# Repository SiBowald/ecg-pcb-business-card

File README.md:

# ECG PCB Business Card

## Table of contents

- [ECG PCB Business Card](#ecg-pcb-business-card)
  - [Intended use / disclaimer](#intended-use--disclaimer)
  - [Battery safety](#battery-safety)
  - [What the card does](#what-the-card-does)
  - [Compatibility (important)](#compatibility-important)
  - [Quick start (battery recommended)](#quick-start-battery-recommended)
  - [How to hold it (signal quality)](#how-to-hold-it-signal-quality)
  - [Powering via NFC energy harvesting (Android only)](#powering-via-nfc-energy-harvesting-android-only)
  - [What you should see](#what-you-should-see)
  - [Files & documentation](#files--documentation)
    - [Project structure](#project-structure)
    - [Running the web app locally](#running-the-web-app-locally)
  - [Quick troubleshooting](#quick-troubleshooting)
  - [Key ICs used](#key-ics-used)
  - [License](#license)
  - [Sponsorship](#sponsorship)

Educational demo: a functional single-lead ECG front end on a business-card-sized PCB.  
It streams the signal to your phone or computer using frequency-modulated ultrasound, decoded in a browser-based web app.

Goal: power it up, open the web app, and see a clean ECG-like waveform within about a minute, without any special lab setup.

---

## Intended use / disclaimer

**This is a DIY educational demo and not a medical device.**  
It is not intended for diagnosis, monitoring, or clinical decisions.

---

## Battery safety

The CR1220 coin cell may be outside of its original packaging. Coin cell batteries are hazardous if swallowed, so **keep them away from children at all times**.

---

## What the card does

- Measures a single-lead ECG using the built-in left/right finger pads
- Streams the signal to a web application via **ultrasound** (microphone permission required)
- Power options:
  - **Battery (recommended)**
  - **NFC energy harvesting (Android only)**

---

## Compatibility (important)

- **iOS:** works best with **Safari**
- **Android:** works best with **Chrome**
- **NFC energy harvesting:** works **only on Android**
  - iOS does not provide a reliable continuous NFC power mode for this use
- If powering via NFC energy harvesting, the phone **must not be charging** (unplug it)

---

## Quick start (battery recommended)

1. **Insert a 3 V CR1220 battery** (rated for at least **500 µA continuous load**).  
   Ensure the **+ (positive) side** faces the same direction as the **+** symbols on the PCB.  
   Do not bend the arms of the PCB battery holder more than necessary.  
   Idle current is **below 1 µA**, so the battery can be left in the holder.

2. **Open the web app**
   - Easiest: tap the phone to the card to open the link (NFC enabled + phone unlocked)
   - Scan the printed QR code
   - Or run locally (see **Files & documentation** below)

3. **In the web application**
   - Press **Start**
   - Allow **microphone access** when prompted

---

## How to hold it (signal quality)

- Place the phone/laptop on a table and rest your elbows to reduce motion.
- Hold the card firmly and press your thumbs onto the pads:
  - Left thumb on the pad marked with the hand icon and **“L”**
  - Right thumb on the pad marked with the hand icon and **“R”**
- Stay still and relax your hands and shoulders (movement causes artifacts).
- Keep the phone close to the card so the microphone picks up the signal reliably.
- Use a quiet room if possible (avoid talking, music, fans, strong background noise).
- Avoid Bluetooth headsets so the browser uses the built-in microphone.

---

## Powering via NFC energy harvesting (Android only)

Use this when you want a “no battery” demo. It is more sensitive to positioning.

1. Make sure the phone is **not charging** (unplug it).
2. Place the card on the **back of the phone**, centered over the phone’s **NFC coil** area.
3. Flip the card upside down as needed so Left/Right orientation is correct while it sits on the phone.
4. Press fingers on the same **L** and **R** pads as in battery mode.
5. If your phone has a metal frame/back, avoid touching metal parts while contacting the pads.

---

## What you should see

You should see a waveform similar to the example printed on the back of the card (below “This is not a medical device.”).

If the signal looks noisy or flat, it is almost always due to:
- Contact pressure
- Hand motion
- Dry skin
- NFC positioning (in harvesting mode)

---

## Files & documentation

### Project structure

- `hardware/ECG_Business_Card/`  
  KiCad project including the schematic, PCB layout, manufacturing files, and documentation assets.

- `web/`  
  Browser-based ECG decoder and viewer.

### Web app

The ECG monitor can be used either locally or directly through GitHub Pages.

**Online:**  
[Open the Ultrasound-based ECG Monitor](https://sibowald.github.io/ecg-pcb-business-card/)

**Locally:**  
Open `web/ultrasound-ecg-monitor/index.html` in a modern web browser.

Microphone access is required for the ECG monitor.

---

## Quick troubleshooting

### No signal / flat line
- Confirm battery orientation (+ matches PCB)
- Press **Start**
- Ensure the browser has **microphone permission**
- Keep the phone very close and ensure it uses the **built-in mic** (disconnect Bluetooth devices)
- Audio sanity check: clapping near the phone should cause a visible change in the signal

### Very noisy signal
- Stay still, increase thumb pressure slightly, relax shoulders
- Try a quieter room
- Dry skin reduces contact: slightly moist fingertips can help
- Avoid touching metal parts of the phone while contacting the pads

### NFC power issues (Android)
- Phone must be unplugged (not charging)
- Align the card over the NFC coil and try small position shifts
- Remove thick cases

---

## Key ICs used

- **AD8233** – Single-lead ECG analog front end (instrumentation amp + filters) used to acquire the ECG signal from the finger pads.
- **LTC6990** – Timer/VCO used to generate the FM ultrasound carrier/modulation for audio-band transmission.
- **ST25DV** – NFC tag used for tap-to-open link and NFC energy harvesting support.

---

## License

See `LICENSE`.

---

## Sponsorship

### Rev. C – Supported by NextPCB

Revision C of the **ECG PCB Business Card** was kindly sponsored by **NextPCB**, who supported the PCB manufacturing and assembly of this revision.

Thank you to NextPCB for supporting this project!

<p align="center">
  
</p>

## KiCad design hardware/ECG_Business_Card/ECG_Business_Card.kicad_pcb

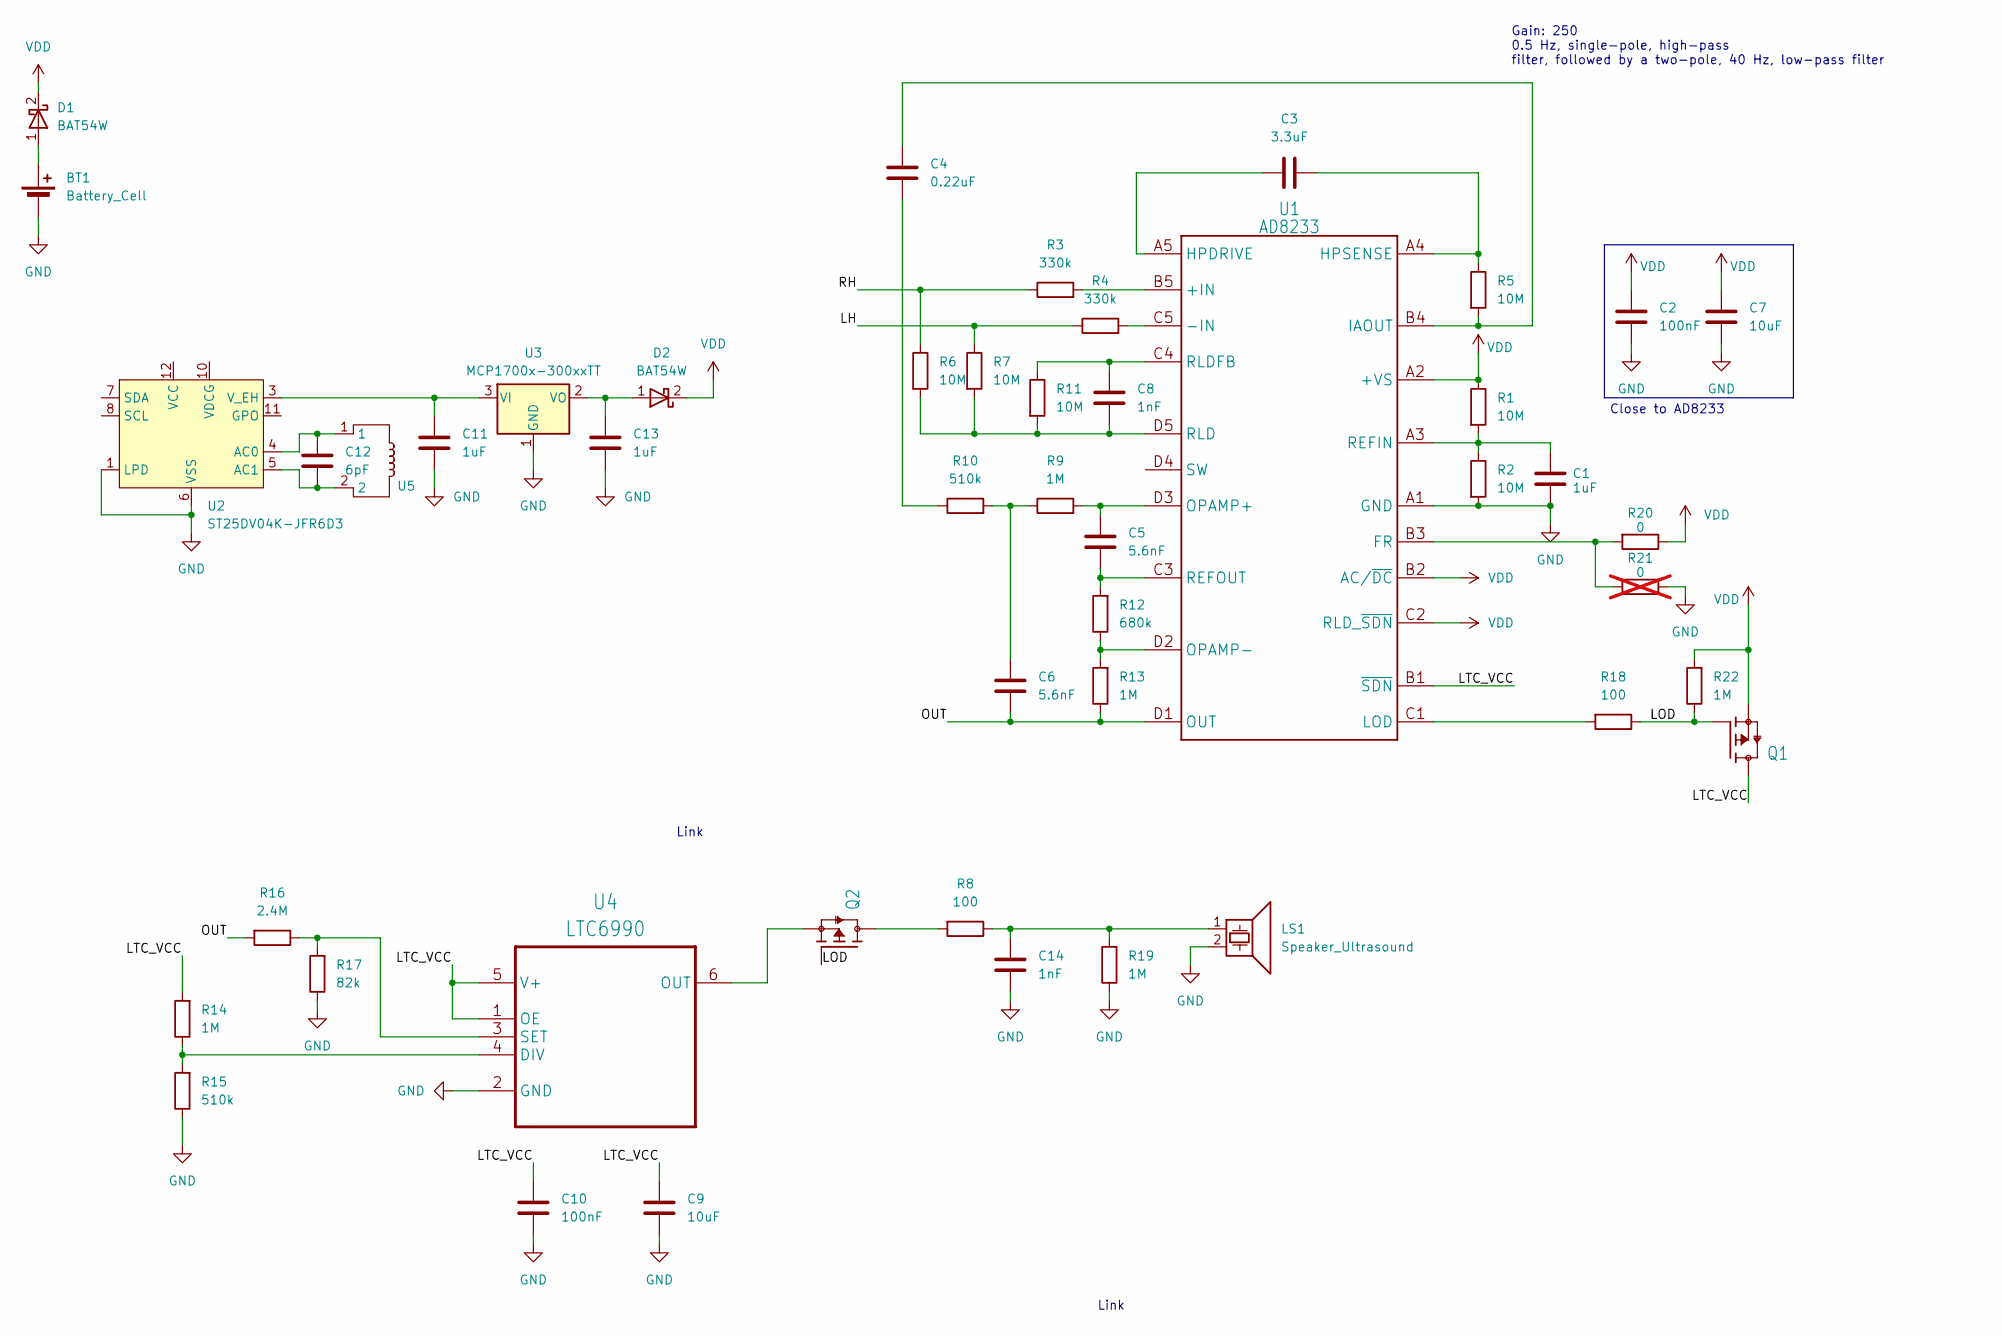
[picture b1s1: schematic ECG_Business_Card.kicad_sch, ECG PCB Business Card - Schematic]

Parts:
BT1: Battery_Cell; CR1220; Part Name CR1220 Battery
C1, C11, C13: 1uF; C_0402_1005Metric; Part Name 1uF 6.3V Ceramic Cap; LCSC C2167130
C2, C10: 100nF; C_0402_1005Metric; Part Name 100nF 16V Ceramic Cap; LCSC C85857
C3: 3.3uF; C_0402_1005Metric; Part Name 10V 3.3uF X5R ±10% 0402 Ceramic Capacit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; LCSC C695126
C4: 0.22uF; C_0402_1005Metric; Part Name 220nF 16V Ceramic Cap; LCSC C126524
C5, C6: 5.6nF; C_0402_1005Metric; Part Name CAP CER 5.6nF 50V C0G 0402; LCSC C3878619
C7, C9: 10uF; C_0402_1005Metric; Part Name 10uF 6.3V Ceramic Cap; LCSC C412251
C8, C14: 1nF; C_0402_1005Metric; Part Name 1nF 50V Ceramic Cap; LCSC C76947
C12: 6pF; C_0402_1005Metric; Part Name 6pF 50V Ceramic Cap; LCSC C1575
D1, D2: BAT54W; SOD-123; Part Name DIODE SCHOTTKY 30V SOD-323; LCSC C22629
LS1: Speaker_Ultrasound; Piezo_12mm; Part Name BUZZER ELEMENT STD 18.5 KHZ 12MM
Q1, Q2: MOSFET P-CH 20V 4.2A SOT23; SOT-723; Part Name MOSFET P-CH 20V 200MA VMT3
R1, R2, R5, R6, R7, R11: 10M; R_0201_0603Metric; Part Name 10M Film Resistor ±1% 0,05W; LCSC C469663
R3, R4: 330k; R_0201_0603Metric; Part Name 330KΩ ±1% 1/20W ±200ppm/℃; LCSC C142017
R8, R18: 100; R_0201_0603Metric; Part Name 100Ω ±1% 1/20W ±200ppm/℃; LCSC C77623
R9, R13, R14, R19, R22: 1M; R_0201_0603Metric; Part Name 1M Film Resistor ±1% 1/20W ±200ppm/℃; LCSC C295786
R10, R15: 510k; R_0201_0603Metric; Part Name 510KΩ ±1% 1/20W ±200ppm/℃; LCSC C295805
R12: 680k; R_0201_0603Metric; Part Name 680KΩ ±1% 1/20W ±200ppm/℃; LCSC C226598
R16: 2.4M; R_0201_0603Metric; Part Name 2.4M Film Resistor ±1% 50mW; LCSC C474580
R17: 82k; R_0201_0603Metric; Part Name 82k Film Resistor ±1% 1/20W ±200ppm/℃; LCSC C273288
R20: 0; R_0201_0603Metric; Part Name 0Ω ±5% 1/20W; LCSC C106228
R21: 0; R_0201_0603Metric; Part Name 0Ω ±5% 1/20W; LCSC C106228; not fitted
U1: AD8233; 20-WLCPS-2MMX1.7MM; Part Name ECG Amplifier IC; LCSC C209349
U2: ST25DV04K-JFR6D3; ST_UFDFPN-12-1EP_3x3mm_P0.5mm_EP1.4x2.55mm; Part Name IC RFID TRANSP 13.56MHZ 12UFDFPN (HQ: S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; LCSC C2654815
U3: MCP1700x-300xxTT; SOT-23; Part Name Low Quiescent Current LDO (HQ: ME6228A3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; LCSC C62244
U4: LTC6990; SOT95P280X100-6N; Part Name Oszillator - Silizium IC 488Hz bis 2MHz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; LCSC C581032
U5: NFC_Antenna

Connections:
/LH: R4.1, R7.1
/LOD: Q1.1 (G), Q2.1 (G), R18.1, R22.1
/LTC_VCC: C9.2, C10.2, Q1.3 (D), R14.2, U1.B1 (~SDN), U4.1 (OE), U4.5 (V+)
/OUT: C6.1, R13.1, R16.2, U1.D1 (OUT)
/RH: R3.1, R6.1
GND: BT1.2 (-), C1.1, C2.1, C7.1, C9.1, C10.1, C11.1, C13.1, C14.1, LS1.2, R2.2, R15.1, R17.1, R19.1, R21.1, U1.A1 (GND), U2.1 (LPD), U2.6 (VSS), U3.1 (GND), U4.2 (GND)
unnamed: BT1.1 (+), D1.1 (A)
unnamed: C4.1, R10.1
unnamed: C6.2, R9.1, R10.2
unnamed: C14.2, LS1.1, R8.1, R19.2
unnamed: C13.2, D2.1 (A), U3.2 (VO)
unnamed: Q2.3 (D), R8.2
unnamed: Q2.2 (S), U4.6 (OUT)
unnamed: R3.2, U1.B5 (+IN)
unnamed: R4.2, U1.C5 (-IN)
unnamed: R20.2, R21.2, U1.B3 (FR)
unnamed: C3.1, U1.A5 (HPDRIVE)
unnamed: C3.2, R5.1, U1.A4 (HPSENSE)
unnamed: C4.2, R5.2, U1.B4 (IAOUT)
unnamed: R18.2, U1.C1 (LOD)
unnamed: C5.2, R9.2, U1.D3 (OPAMP+)
unnamed: R12.1, R13.2, U1.D2 (OPAMP-)
unnamed: C1.2, R1.2, R2.1, U1.A3 (REFIN)
unnamed: C5.1, R12.2, U1.C3 (REFOUT)
unnamed: C8.1, R6.2, R7.2, R11.2, U1.D5 (RLD)
unnamed: C8.2, R11.1, U1.C4 (RLDFB)
unnamed: C12.2, U2.4 (AC0), U5.1
unnamed: C12.1, U2.5 (AC1), U5.2
unnamed: C11.2, U2.3 (V_EH), U3.3 (VI)
unnamed: R14.1, R15.2, U4.4 (DIV)
unnamed: R16.1, R17.2, U4.3 (SET)
VDD: C2.2, C7.2, D1.2 (K), D2.2 (K), Q1.2 (S), R1.1, R20.1, R22.2, U1.A2 (+VS), U1.B2 (AC/~DC), U1.C2 (RLD_~SDN)

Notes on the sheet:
Link
Close to AD8233
Gain: 250 0.5 Hz, single-pole, high-pass filter, followed by a two-pole, 40 Hz, low-pass filter

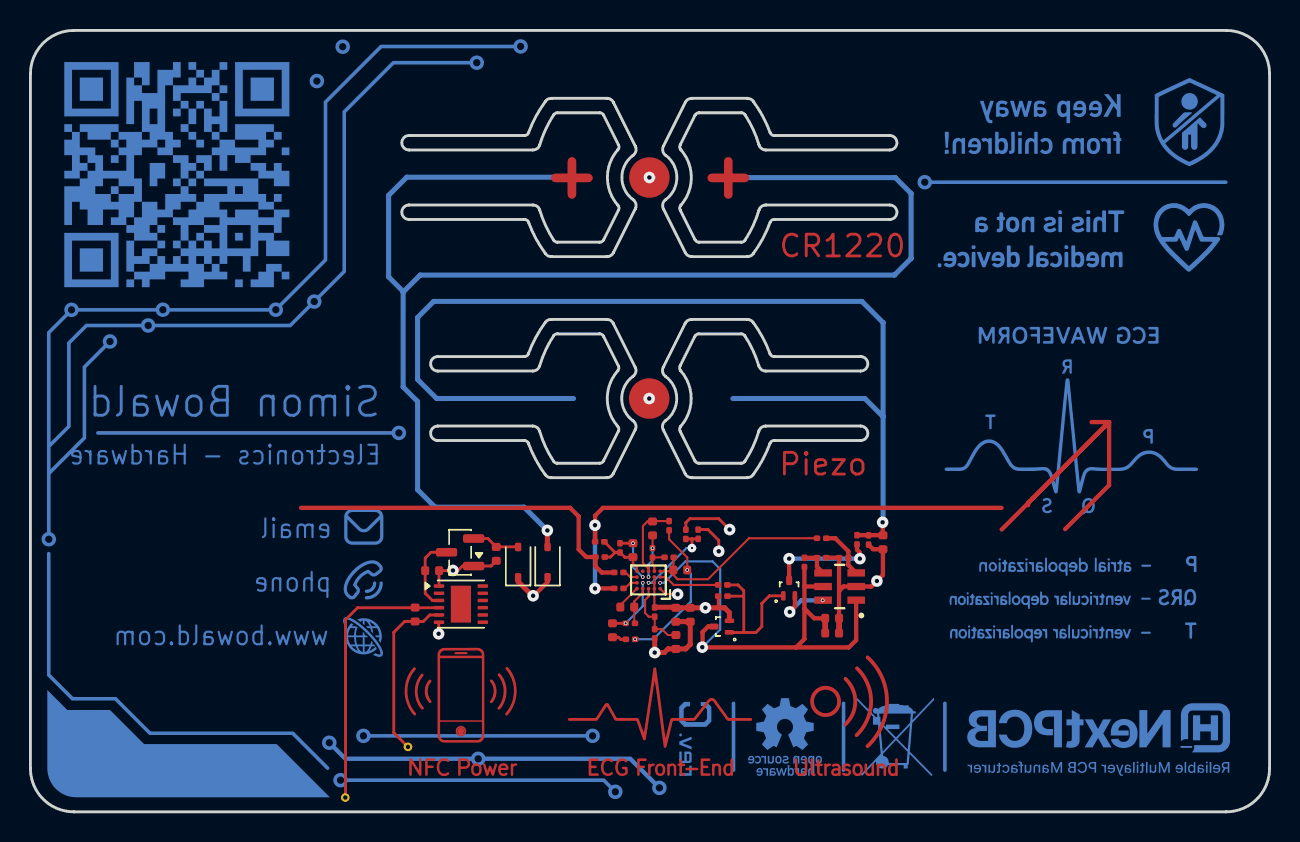
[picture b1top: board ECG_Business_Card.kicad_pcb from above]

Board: 4 copper layers, 85.6 x 54.0 mm, 47 parts (0 on the bottom side), 32 nets.

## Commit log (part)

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2026-02-04 Initial commit: hardware + web app + docs
    Includes MIT license for software, CERN-OHL-P-2.0 for hardware, and initial browser ECG viewer files.
2026-02-11 Add KiCad v9 hardware project and initial README
    Adds the new KiCad 9 design files (schematic + PCB) under hardware/ECG_Business_Card_v3/ along with project libraries/assets, and adds a professional README.md with quick start, compatibility notes, 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
2026-02-12 Add Renders
2026-02-13 Add Demo Image
2026-02-13 Add NFC test photos
2026-03-29 Add pictures
